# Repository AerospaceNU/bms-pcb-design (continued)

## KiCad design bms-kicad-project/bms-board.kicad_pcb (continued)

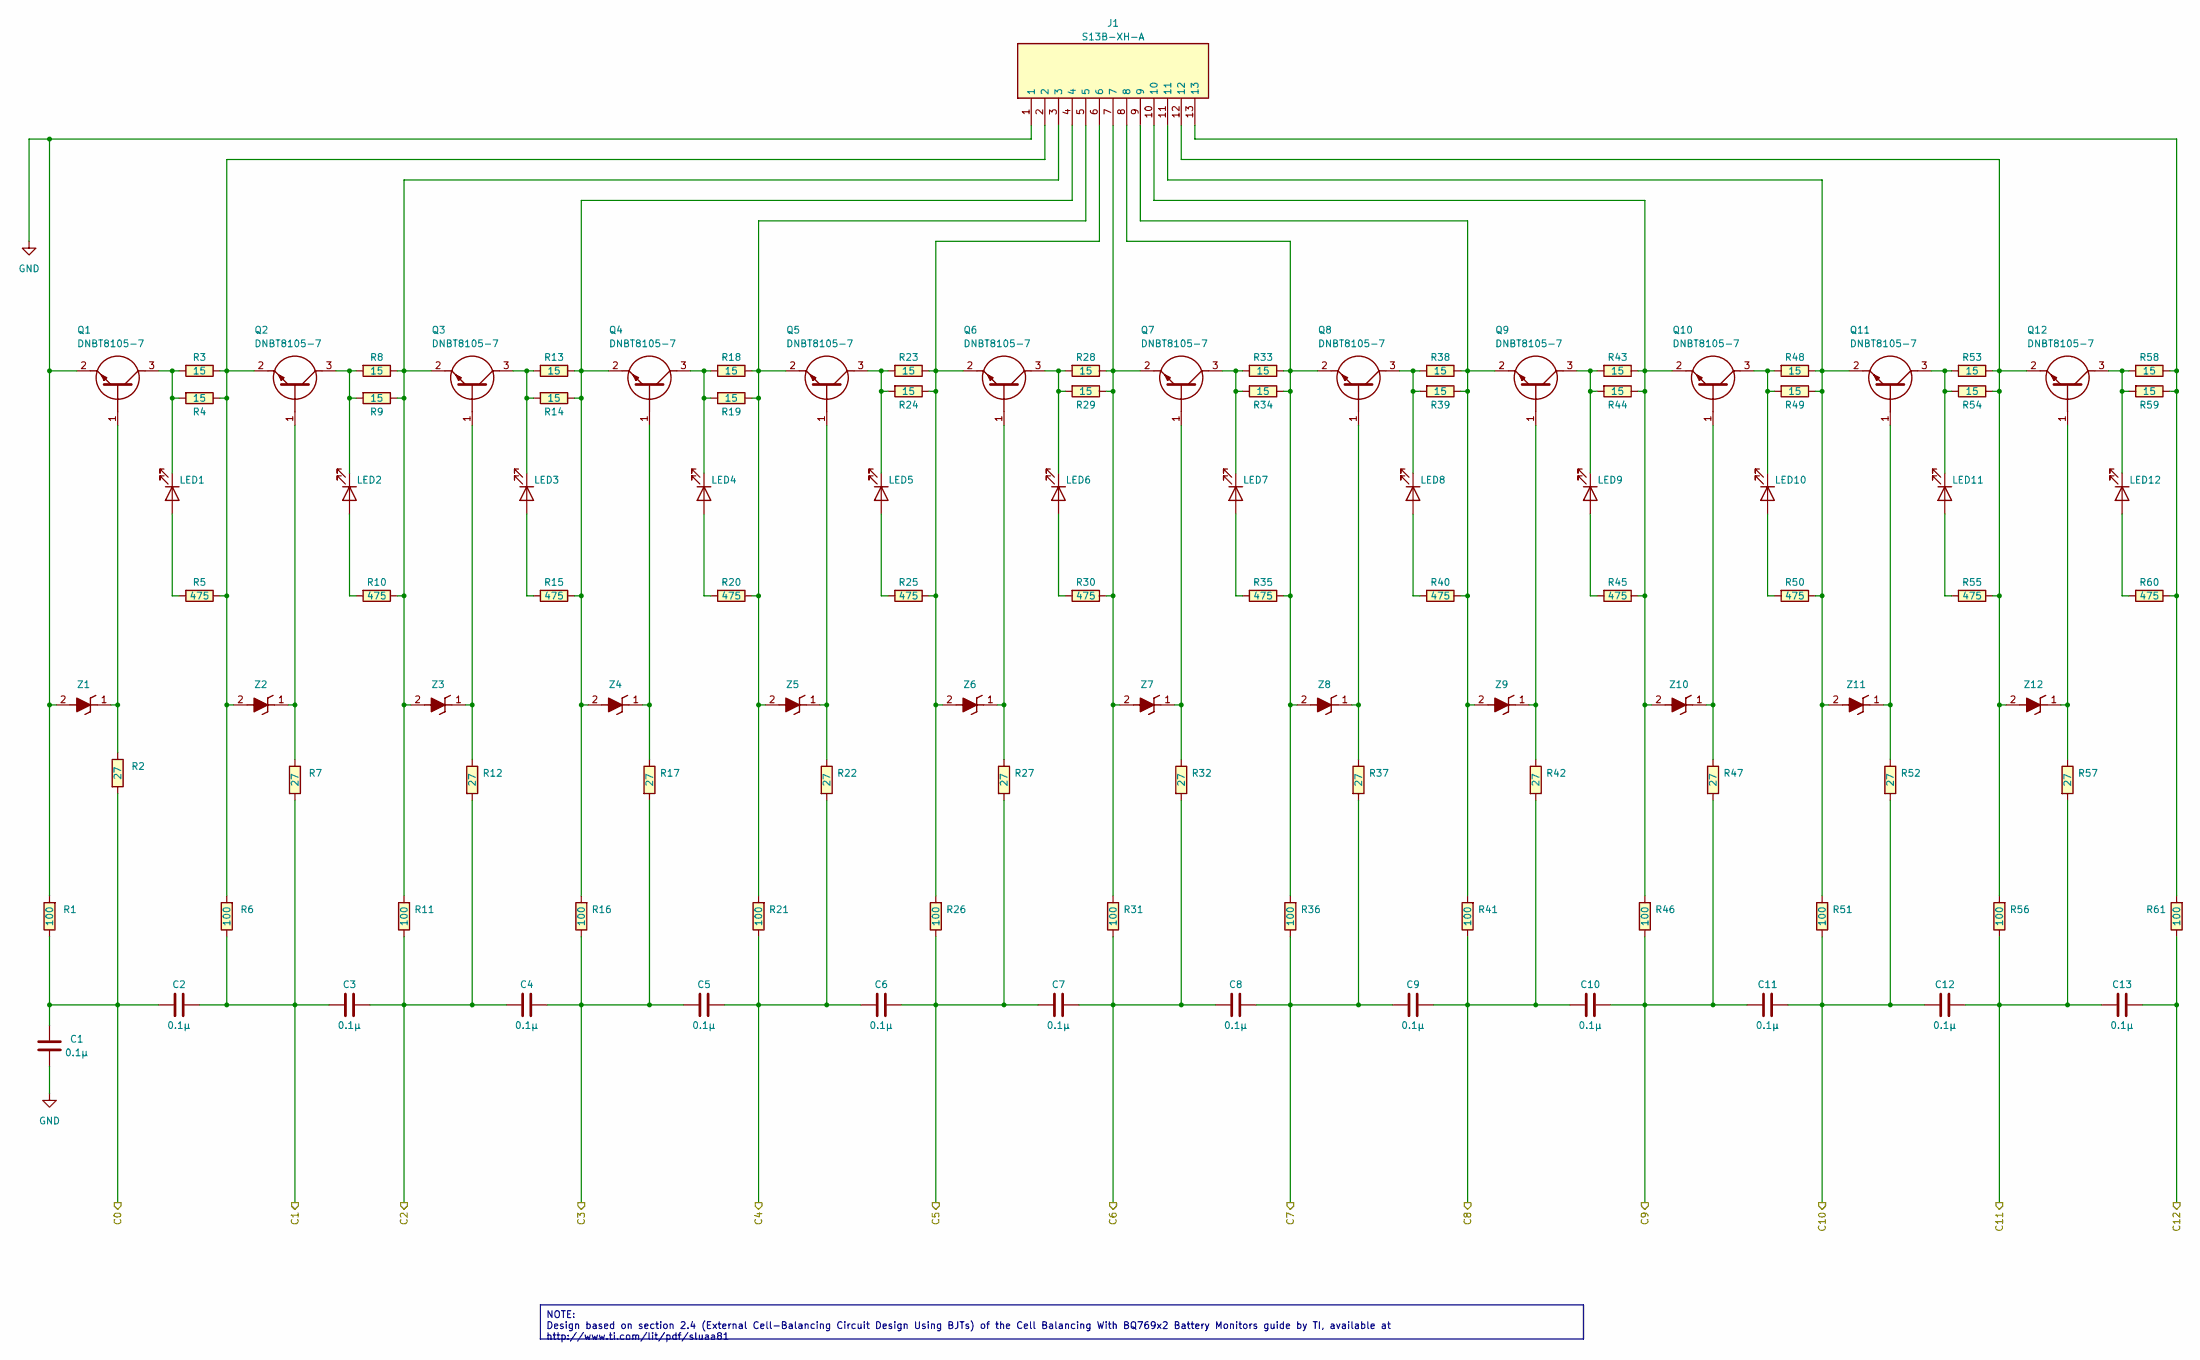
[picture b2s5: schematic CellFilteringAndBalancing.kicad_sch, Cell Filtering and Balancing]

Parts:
C1, C2, C3, C4, C5, C6, C7, C8, C9, C10, C11, C12, C13: 0.1µ; CAP_GCJ-18_MUR; Manufacturer Part Number GCJ188R72A104KA01D
J1: S13B-XH-A; S13BXHALFSN; Manufacturer Part Number S13B-XH-A
LED1, LED2, LED3, LED4, LED5, LED6, LED7, LED8, LED9, LED10, LED11, LED12: LTST-C170KRKT; LEDC2012X120N; Mouser Part Number 859-LTST-C170KRKT
Q1, Q2, Q3, Q4, Q5, Q6, Q7, Q8, Q9, Q10, Q11, Q12: DNBT8105-7; SOT95P240X105-3N; Manufacturer Part Number DNBT8105-7; Mouser Part Number 621-DNBT8105-7
R1, R6, R11, R16, R21, R26, R31, R36, R41, R46, R51, R56, R61: 100; RESC2012X50N; Mouser Part Number 71-CRCW0805-100-E3
R2, R7, R12, R17, R22, R27, R32, R37, R42, R47, R52, R57: 27; RC0805N_YAG; Manufacturer Part Number RC0805FR-0727RL
R3, R4, R8, R9, R13, R14, R18, R19, R23, R24, R28, R29, R33, R34, R38, R39, R43, R44, R48, R49, R53, R54, R58, R59: 15; RES_R1632_ROM; Manufacturer Part Number LTR18EZPF15R0
R5, R10, R15, R20, R25, R30, R35, R40, R45, R50, R55, R60: 475; RESC2012X50N; Mouser Part Number 71-CRCW0805-475-E3
Z1, Z2, Z3, Z4, Z5, Z6, Z7, Z8, Z9, Z10, Z11, Z12: BZT52C5V6T-7; BZT52C5V6T7; Manufacturer Part Number BZT52C5V6T-7; Mouser Part Number 621-BZT52C5V6T-7

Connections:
/Battery Stack Monitor/C0: C1.2, C2.2, R1.2, R2.1; also elsewhere on the board
/Battery Stack Monitor/C1: C2.1, C3.1, R6.2, R7.1; also elsewhere on the board
/Battery Stack Monitor/C2: C3.2, C4.1, R11.2, R12.1; also elsewhere on the board
/Battery Stack Monitor/C3: C4.2, C5.1, R16.2, R17.1; also elsewhere on the board
/Battery Stack Monitor/C4: C5.2, C6.1, R21.2, R22.1; also elsewhere on the board
/Battery Stack Monitor/C5: C6.2, C7.1, R26.2, R27.1; also elsewhere on the board
/Battery Stack Monitor/C6: C7.2, C8.1, R31.2, R32.1; also elsewhere on the board
/Battery Stack Monitor/C7: C8.2, C9.1, R36.2, R37.1; also elsewhere on the board
/Battery Stack Monitor/C8: C9.2, C10.1, R41.2, R42.1; also elsewhere on the board
/Battery Stack Monitor/C9: C10.2, C11.1, R46.2, R47.1; also elsewhere on the board
/Battery Stack Monitor/C10: C11.2, C12.1, R51.2, R52.1; also elsewhere on the board
/Battery Stack Monitor/C11: C12.2, C13.1, R56.2, R57.1; also elsewhere on the board
/Battery Stack Monitor/C12: C13.2, R61.2; also elsewhere on the board
GND: C1.1, J1.1, Q1.2 (E), R1.1, Z1.2 (A); also elsewhere on the board
unnamed: J1.13, R58.2, R59.2, R60.2, R61.1
unnamed: LED1.2 (A), R5.1
unnamed: LED1.1 (K), Q1.3 (C), R3.1, R4.1
unnamed: LED2.2 (A), R10.1
unnamed: LED2.1 (K), Q2.3 (C), R8.1, R9.1
unnamed: LED3.2 (A), R15.1
unnamed: LED3.1 (K), Q3.3 (C), R13.1, R14.1
unnamed: LED4.2 (A), R20.1
unnamed: LED4.1 (K), Q4.3 (C), R18.1, R19.1
unnamed: LED5.2 (A), R25.1
unnamed: LED5.1 (K), Q5.3 (C), R23.1, R24.1
unnamed: LED6.2 (A), R30.1
unnamed: LED6.1 (K), Q6.3 (C), R28.1, R29.1
unnamed: LED7.2 (A), R35.1
unnamed: LED7.1 (K), Q7.3 (C), R33.1, R34.1
unnamed: LED8.2 (A), R40.1
unnamed: LED8.1 (K), Q8.3 (C), R38.1, R39.1
unnamed: LED9.2 (A), R45.1
unnamed: LED9.1 (K), Q9.3 (C), R43.1, R44.1
unnamed: LED10.2 (A), R50.1
unnamed: LED10.1 (K), Q10.3 (C), R48.1, R49.1
unnamed: LED11.2 (A), R55.1
unnamed: LED11.1 (K), Q11.3 (C), R53.1, R54.1
unnamed: LED12.2 (A), R60.1
unnamed: LED12.1 (K), Q12.3 (C), R58.1, R59.1
unnamed: Q1.1 (B), R2.2, Z1.1 (K)
unnamed: Q2.1 (B), R7.2, Z2.1 (K)
unnamed: J1.2, Q2.2 (E), R3.2, R4.2, R5.2, R6.1, Z2.2 (A)
unnamed: Q3.1 (B), R12.2, Z3.1 (K)
unnamed: J1.3, Q3.2 (E), R8.2, R9.2, R10.2, R11.1, Z3.2 (A)
unnamed: Q4.1 (B), R17.2, Z4.1 (K)
unnamed: J1.4, Q4.2 (E), R13.2, R14.2, R15.2, R16.1, Z4.2 (A)
unnamed: Q5.1 (B), R22.2, Z5.1 (K)
unnamed: J1.5, Q5.2 (E), R18.2, R19.2, R20.2, R21.1, Z5.2 (A)
unnamed: Q6.1 (B), R27.2, Z6.1 (K)
unnamed: J1.6, Q6.2 (E), R23.2, R24.2, R25.2, R26.1, Z6.2 (A)
unnamed: Q7.1 (B), R32.2, Z7.1 (K)
unnamed: J1.7, Q7.2 (E), R28.2, R29.2, R30.2, R31.1, Z7.2 (A)
unnamed: Q8.1 (B), R37.2, Z8.1 (K)
unnamed: J1.8, Q8.2 (E), R33.2, R34.2, R35.2, R36.1, Z8.2 (A)
unnamed: Q9.1 (B), R42.2, Z9.1 (K)
unnamed: J1.9, Q9.2 (E), R38.2, R39.2, R40.2, R41.1, Z9.2 (A)
unnamed: Q10.1 (B), R47.2, Z10.1 (K)
unnamed: J1.10, Q10.2 (E), R43.2, R44.2, R45.2, R46.1, Z10.2 (A)
unnamed: Q11.1 (B), R52.2, Z11.1 (K)
unnamed: J1.11, Q11.2 (E), R48.2, R49.2, R50.2, R51.1, Z11.2 (A)
unnamed: Q12.1 (B), R57.2, Z12.1 (K)
unnamed: J1.12, Q12.2 (E), R53.2, R54.2, R55.2, R56.1, Z12.2 (A)

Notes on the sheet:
NOTE: Design based on section 2.4 (External Cell-Balancing Circuit Design Using BJTs) of the Cell Balancing With BQ769x2 Battery Monitors guide by TI, available at http://www.ti.com/lit/pdf/sluaa81

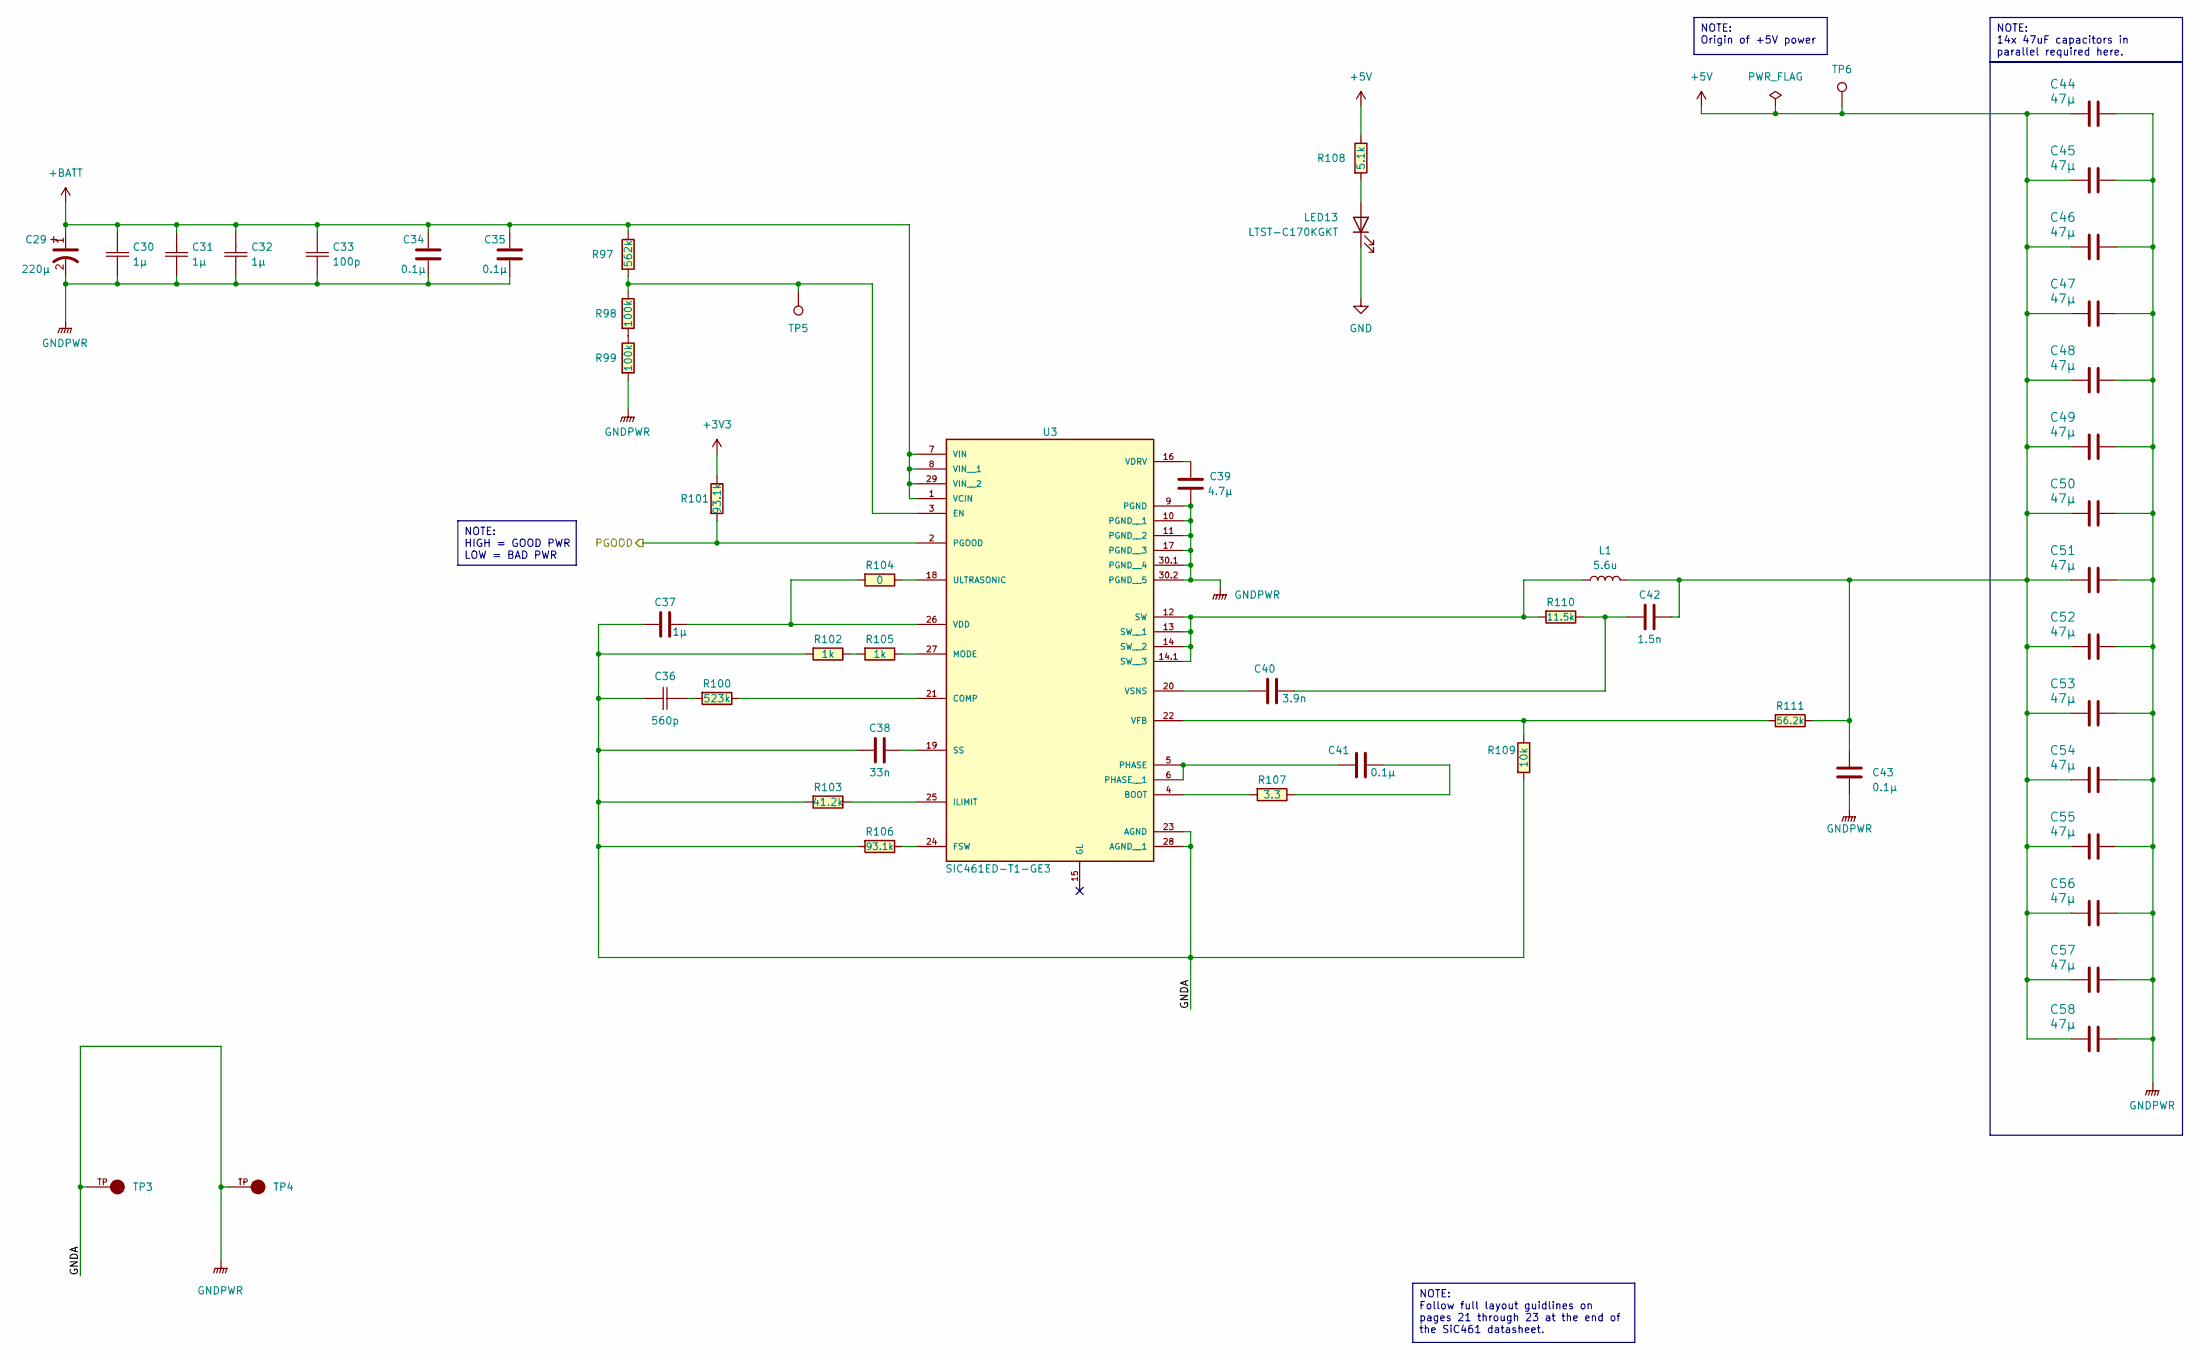
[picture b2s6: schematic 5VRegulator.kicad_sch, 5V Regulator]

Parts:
C29: 220µ; CAPPRD500W60D1000H2500; PARTREV 28-FEB-20
C30, C31, C32: 1µ; CAP_CL31_SAM; Manufacturer Part Number CL31B105KCHNNNE
C33: 100p; CAPC220145_88N_KEM; Manufacturer Part Number C0805C101J1GACTU
C34, C35: 0.1µ; CAP_GCJ-18_MUR; Manufacturer Part Number GCJ188R72A104KA01D
C36: 560p; CAP_CC0805_YAG; Manufacturer Part Number CC0805JRNPO9BN561
C37: 1µ; CAPC1608X90N; Manufacturer Part Number GCM188R71C105KA64D
C38: 33n; CAPC2012X94N; Manufacturer Part Number KGM21NR71E333KT
C39: 4.7µ; CAPC2012X145N; Manufacturer Part Number GCM21BC71E475KE36L
C40: 3.9n; G-21_MUR; Manufacturer Part Number GRM2165C1H392JA01D
C41, C43: 0.1µ; CAP_GCJ-18_MUR; Manufacturer_Part_Number GCJ188R72A104KA01D
C42: 1.5n; G-21_MUR; Manufacturer Part Number GRM2165C1H152JA01D
C44, C45, C46, C47, C48, C49, C50, C51, C52, C53, C54, C55, C56, C57, C58: 47µ; G-32_MUR; Manufacturer Part Number GRM32ER71A476KE15L
L1: 5.6u; IND_IHLP-6767GZ_VIS; Manufacturer Part Number IHLP6767GZER5R6M01
LED13: LTST-C170KGKT; LED_LTST-C170KGKT_LTO; Manufacturer Part Number LTST-C170KGKT
R97: 562k; RESC2012X60N; Manufacturer Part Number RC0805FR-07562KL
R98, R99: 100k; RESC2012X60N; Manufacturer Part Number RC0805FR-07100KL
R100: 523k; RC0805N_YAG; Manufacturer Part Number RC0805FR-07523KL
R101, R106: 93.1k; RESC2012X60N; Manufacturer Part Number RC0805FR-0793K1L
R102, R105: 1k; RC0805N_YAG; Manufacturer_Part_Number RC0805FR-071KL
R103: 41.2k; RC0805N_VIS; Manufacturer Part Number CRCW080541K2FKEA
R104: 0; RES_CRCW_0805_VIS; Manufacturer Part Number CRCW08050000Z0EA
R107: 3.3; RESC1608X55N; Manufacturer Part Number RK73H1JTTD3R30F
R108: 5.1k; RESC2012X60N; Manufacturer Part Number RC0805JR-075K1L
R109: 10k; KOA_Speer-RK73H2A-0-0-MFG; power rating 0.125W; tolerance 1%; Manufacturer Part Number RK73H2ATTD1002F; digikey description RES 10K OHM 1% 1/4W 0805
R110: 11.5k; RC0805N_YAG; Manufacturer Part Number RC0805FR-0711K5L
R111: 56.2k; RC0805N_YAG; Manufacturer Part Number RC0805FR-0756K2L
TP3, TP4: 5261; KEYSTONE_5261; PARTREV H
TP5, TP6: TestPoint_Pad_D1.0mm
U3: SIC461ED-T1-GE3; CONV_SIC461ED-T1-GE3; PARTREV M

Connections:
+3V3: R101.2; also elsewhere on the board
+5V: C42.2, C43.2, C44.2, C45.2, C46.2, C47.2, C48.2, C49.2, C50.2, C51.2, C52.2, C53.2, C54.2, C55.2, C56.2, C57.2, C58.2, L1.2, R108.2, R111.2, TP6.1; also elsewhere on the board
+BATT: C29.1, C30.2, C31.2, C32.2, C33.2, C34.2, C35.2, R97.2, U3.1 (VCIN), U3.7 (VIN), U3.8 (VIN__1), U3.29 (VIN__2); also elsewhere on the board
/5V Regulator/PGOOD: R101.1, U3.2 (PGOOD); also elsewhere on the board
GND: C29.2 (N), C30.1, C31.1, C32.1, C33.1, C34.1, C35.1, C36.1, C37.2, C38.1, C39.1, C43.1, C44.1, C45.1, C46.1, C47.1, C48.1, C49.1, C50.1, C51.1, C52.1, C53.1, C54.1, C55.1, C56.1, C57.1, C58.1, LED13.1 (K), R99.1, R102.1, R103.1, R106.1, R109.1, TP3.TP, TP4.TP, U3.9 (PGND), U3.10 (PGND__1), U3.11 (PGND__2), U3.17 (PGND__3), U3.23 (AGND), U3.28 (AGND__1), U3.30.1 (PGND__4), U3.30.2 (PGND__5); also elsewhere on the board
unnamed: C36.2, R100.1
unnamed: C40.2, C42.1, R110.2
unnamed: C41.1, R107.2
unnamed: LED13.2 (A), R108.1
unnamed: R98.1, R99.2
unnamed: R102.2, R105.1
unnamed: R107.1, U3.4 (BOOT)
unnamed: R100.2, U3.21 (COMP)
unnamed: R97.1, R98.2, TP5.1, U3.3 (EN)
unnamed: R106.2, U3.24 (FSW)
unnamed: R103.2, U3.25 (ILIMIT)
unnamed: R105.2, U3.27 (MODE)
unnamed: C41.2, U3.5 (PHASE), U3.6 (PHASE__1)
unnamed: C38.2, U3.19 (SS)
unnamed: L1.1, R110.1, U3.12 (SW), U3.13 (SW__1), U3.14 (SW__2), U3.14.1 (SW__3)
unnamed: R104.2, U3.18 (ULTRASONIC)
unnamed: C37.1, R104.1, U3.26 (VDD)
unnamed: C39.2, U3.16 (VDRV)
unnamed: R109.2, R111.1, U3.22 (VFB)
unnamed: C40.1, U3.20 (VSNS)

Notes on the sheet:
NOTE: 14x 47uF capacitors in parallel required here.
NOTE: Origin of +5V power
NOTE: Follow full layout guidlines on pages 21 through 23 at the end of the SiC461 datasheet.
NOTE: HIGH = GOOD PWR LOW = BAD PWR

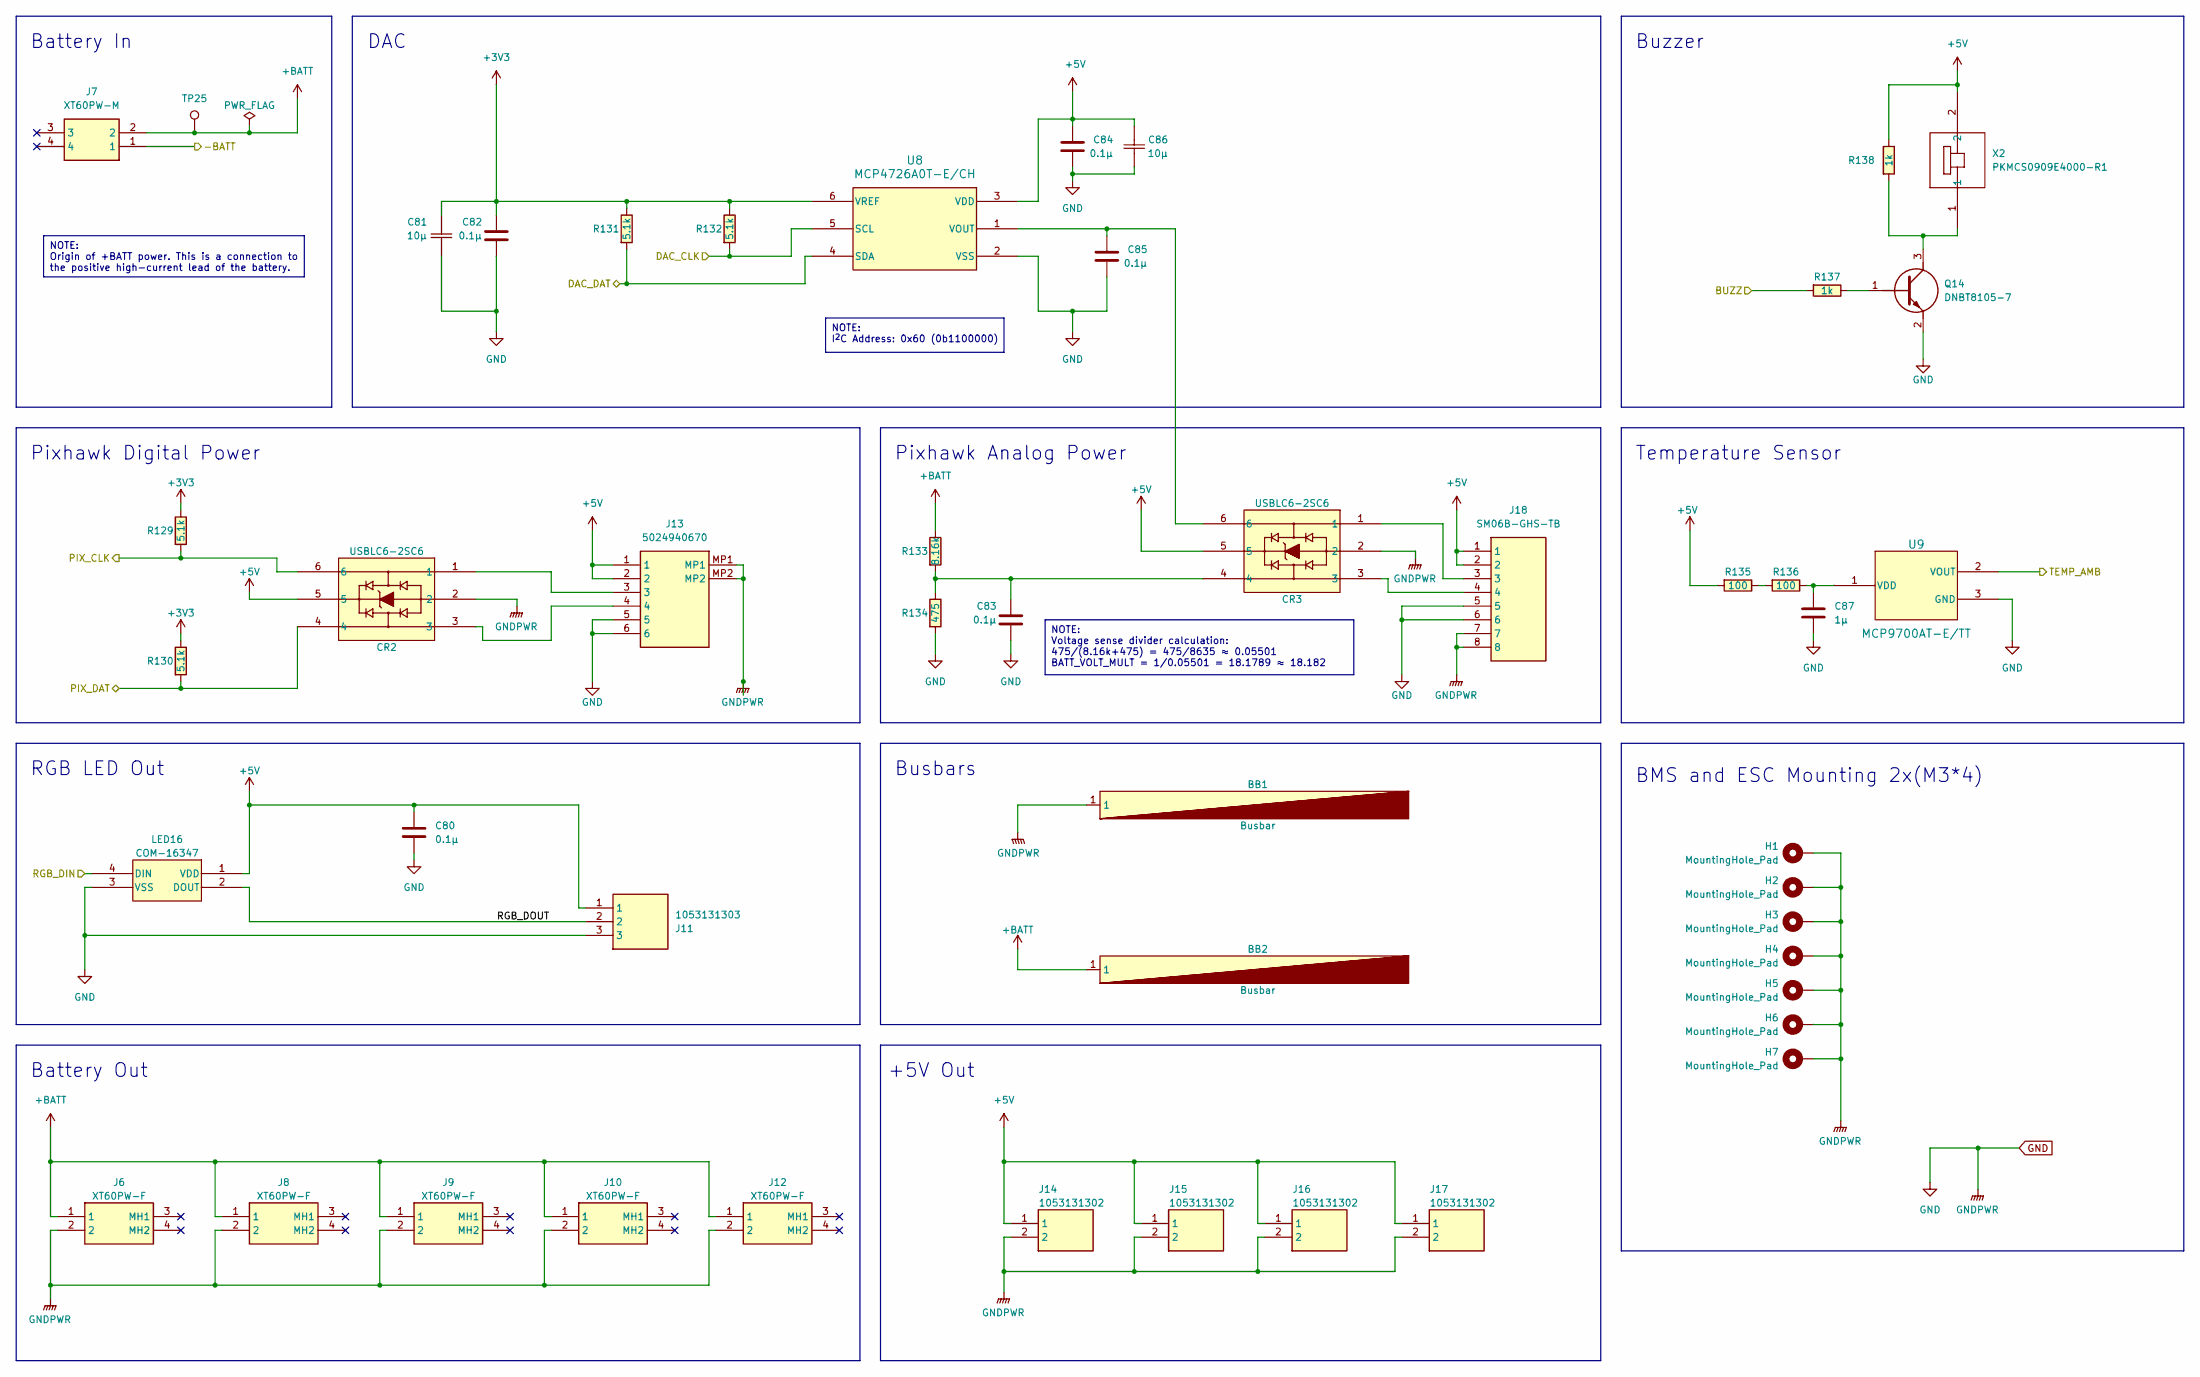
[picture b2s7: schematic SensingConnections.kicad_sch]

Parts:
BB1: Busbar; BUSBAR_SHORT; Manufacturer Part Number T2 Copper
BB2: Busbar; BUSBAR_LONG; Manufacturer Part Number T2 Copper
C80, C82, C83, C84, C85: 0.1µ; CAP_GCJ-18_MUR; Manufacturer Part Number GCJ188R72A104KA01D
C81, C86: 10µ; CAP_CL21B106KOQNNNE_SAM; Manufacturer Part Number CL21B106KOQNNNE
C87: 1µ; CAPC1608X90N; Manufacturer Part Number GCM188R71C105KA64D
CR2, CR3: USBLC6-2SC6; SOT23-6L_STM; Manufacturer Part Number USBLC6-2SC6
H1, H2, H3, H4, H5, H6, H7: MountingHole_Pad; MountingHole_3.2mm_M3_ISO14580_Pad
J6, J8, J9, J10: XT60PW-F; XT60PWF; Manufacturer Part Number XT60PW-F
J7: XT60PW-M; XT60PWM_Pad; Manufacturer Part Number XT60PW-M
J11: 1053131303; 105313YY03; Manufacturer Part Number 1053131303
J12: XT60PW-F; XT60PWF_Pad; Manufacturer Part Number XT60PW-F
J13: 5024940670; Manufacturer Part Number 5024940670; Mouser Part Number 538-502494-0670
J14, J15, J16, J17: 1053131302; 105313YY02; Manufacturer Part Number 1053131302
J18: SM06B-GHS-TB; Manufacturer Part Number SM06B-GHS-TB(LF)(SN); Mouser Part Number 306-SM06BGHSTBLFSN
LED16: COM-16347; COM-16347_SPK; Manufacturer Part Number COM-16347
Q14: DNBT8105-7; SOT95P240X105-3N; Manufacturer Part Number DNBT8105-7; Mouser Part Number 621-DNBT8105-7
R129, R130, R131, R132: 5.1k; RESC2012X60N; Manufacturer Part Number RC0805JR-075K1L
R133: 8.16k; RC0805N_YAG; Manufacturer Part Number RT0805BRD078K16L
R134: 475; RESC2012X50N; Mouser Part Number 71-CRCW0805-475-E3
R135, R136: 100; RESC2012X50N; Mouser Part Number 71-CRCW0805-100-E3
R137, R138: 1k; RC0805N_YAG; Manufacturer Part Number RC0805FR-071KL
TP25: TestPoint_Pad_D1.0mm
U8: MCP4726A0T-E/CH; SOT-23-6_MC_MCH; Manufacturer Part Number MCP4726A0T-E/CH
U9: MCP9700AT-E/TT; SOT-23_MC_MCH; Manufacturer Part Number MCP9700AT-E/TT
X2: PKMCS0909E4000-R1; PKMCS0909E4000-R1_MUR; Manufacturer Part Number PKMCS0909E4000-R1

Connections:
+3V3: C81.2, C82.2, R129.2, R130.2, R131.2, R132.2, U8.6 (VREF); also elsewhere on the board
+5V: C80.2, C84.2, C86.2, CR2.5, CR3.5, J11.1, J13.1, J13.2, J14.1, J15.1, J16.1, J17.1, J18.1, J18.2, LED16.1 (VDD), R135.1, R138.2, U8.3 (VDD), X2.2; also elsewhere on the board
+BATT: BB2.1, J6.1, J7.2, J8.1, J9.1, J10.1, J12.1, R133.1, TP25.1; also elsewhere on the board
/Battery Stack Monitor/-BATT: J7.1; also elsewhere on the board
/External Connections and Sensing/BUZZ: R137.1; also elsewhere on the board
/External Connections and Sensing/DAC_CLK: R132.1, U8.5 (SCL); also elsewhere on the board
/External Connections and Sensing/DAC_DAT: R131.1, U8.4 (SDA); also elsewhere on the board
/External Connections and Sensing/PIX_CLK: CR2.6, R129.1; also elsewhere on the board
/External Connections and Sensing/PIX_DAT: CR2.4, R130.1; also elsewhere on the board
/External Connections and Sensing/RGB_DIN: LED16.4 (DIN); also elsewhere on the board
/External Connections and Sensing/RGB_DOUT: J11.2, LED16.2 (DOUT)
/External Connections and Sensing/TEMP_AMB: U9.2 (VOUT); also elsewhere on the board
GND: BB1.1, C80.1, C81.1, C82.1, C83.1, C84.1, C85.1, C86.1, C87.1, CR2.2, CR3.2, H1.1, H2.1, H3.1, H4.1, H5.1, H6.1, H7.1, J6.2, J8.2, J9.2, J10.2, J11.3, J12.2, J13.5, J13.6, J13.MP1, J13.MP2, J14.2, J15.2, J16.2, J17.2, J18.5, J18.6, J18.7, J18.8, LED16.3 (VSS), Q14.2 (E), R134.1, U8.2 (VSS), U9.3 (GND); also elsewhere on the board
unnamed: C83.2, CR3.4, R133.2, R134.2
unnamed: CR2.1, J13.3
unnamed: CR2.3, J13.4
unnamed: CR3.1, J18.3
unnamed: CR3.3, J18.4
unnamed: Q14.1 (B), R137.2
unnamed: Q14.3 (C), R138.1, X2.1
unnamed: R135.2, R136.1
unnamed: C85.2, CR3.6, U8.1 (VOUT)
unnamed: C87.2, R136.2, U9.1 (VDD)

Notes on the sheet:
NOTE: Voltage sense divider calculation: 475/(8.16k+475) = 475/8635 ≈ 0.05501 BATT_VOLT_MULT = 1/0.05501 = 18.1789 ≈ 18.182
NOTE: I^{2}C Address: 0x60 (0b1100000)
NOTE: Origin of +BATT power. This is a connection to the positive high-current lead of the battery.
Battery In
Buzzer
RGB LED Out
Battery Out
DAC
Pixhawk Analog Power
BMS and ESC Mounting 2x(M3*4)
Pixhawk Digital Power
Temperature Sensor
+5V Out
Busbars

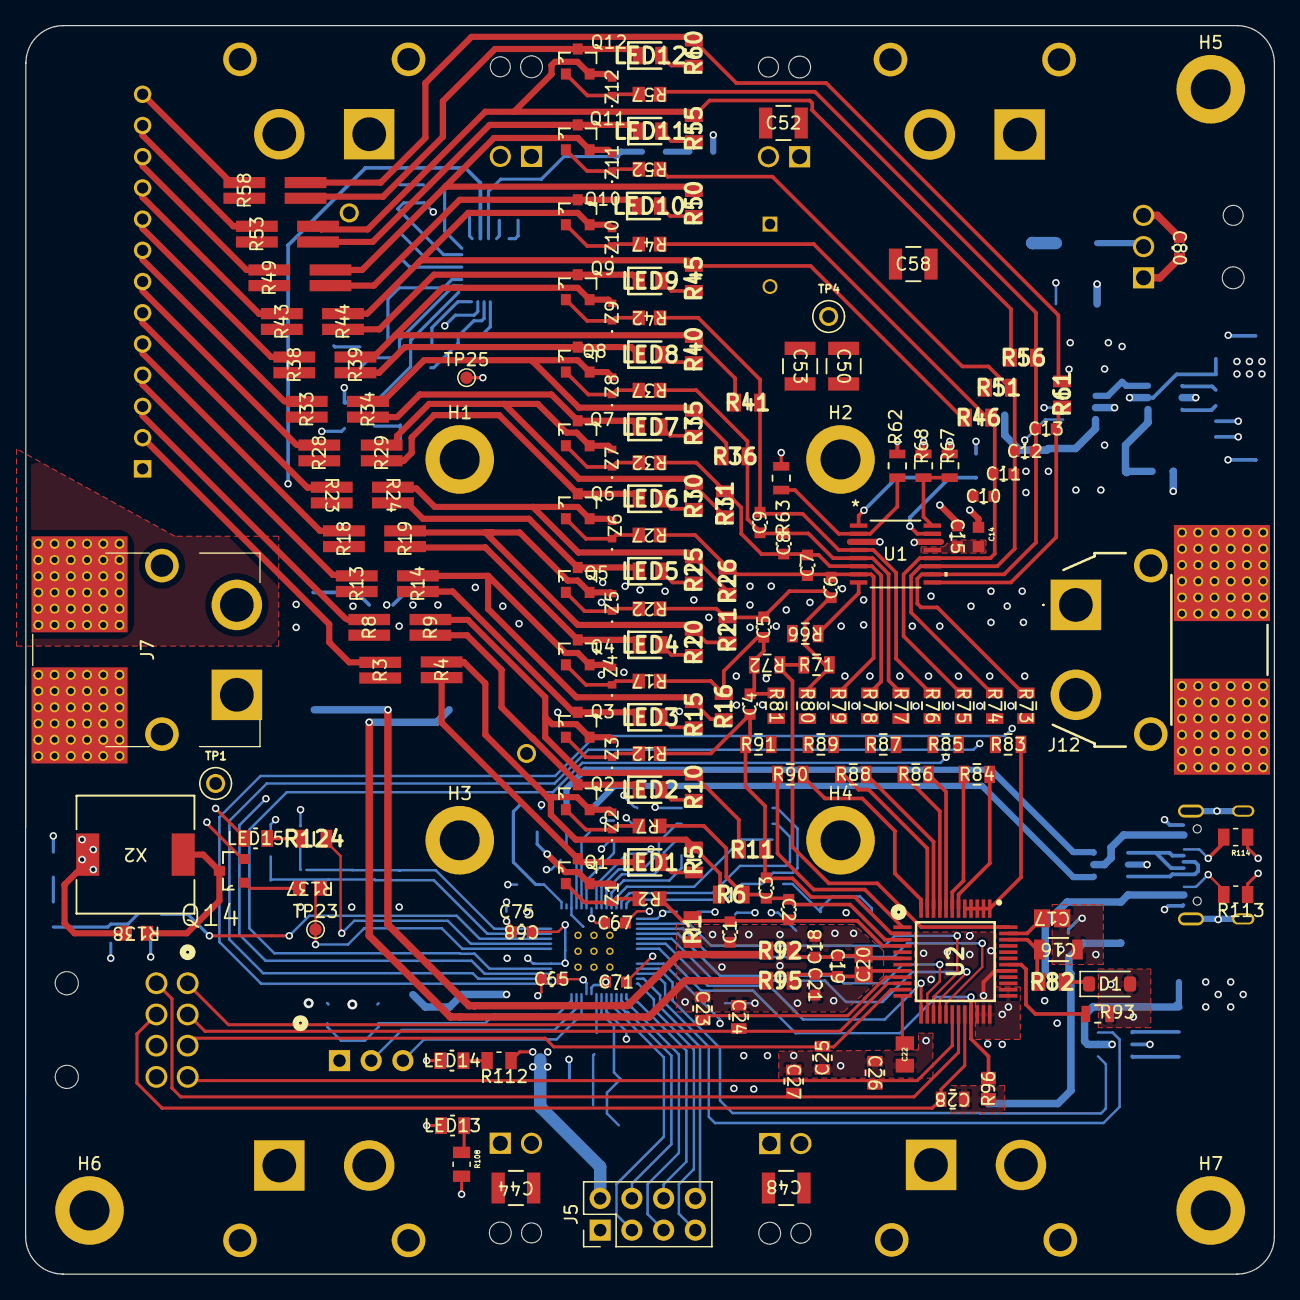
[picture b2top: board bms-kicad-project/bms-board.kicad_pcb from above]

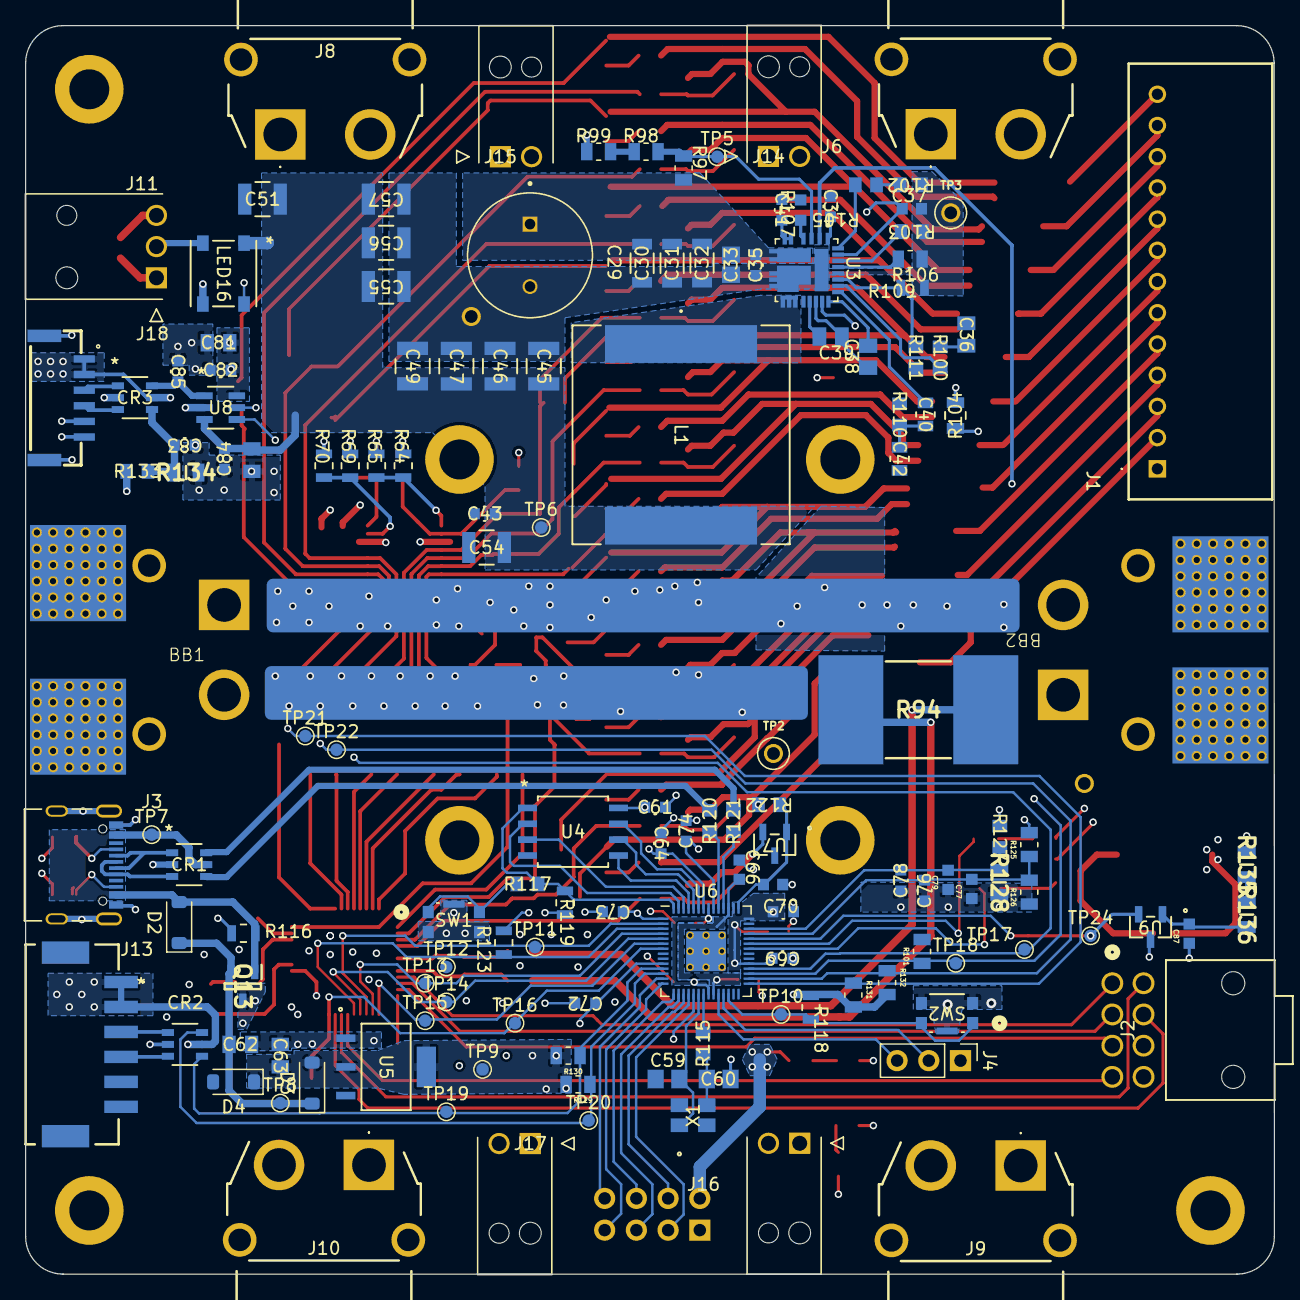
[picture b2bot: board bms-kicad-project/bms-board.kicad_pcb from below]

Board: 6 copper layers, 100.0 x 100.0 mm, 340 parts (145 on the bottom side), 174 nets.

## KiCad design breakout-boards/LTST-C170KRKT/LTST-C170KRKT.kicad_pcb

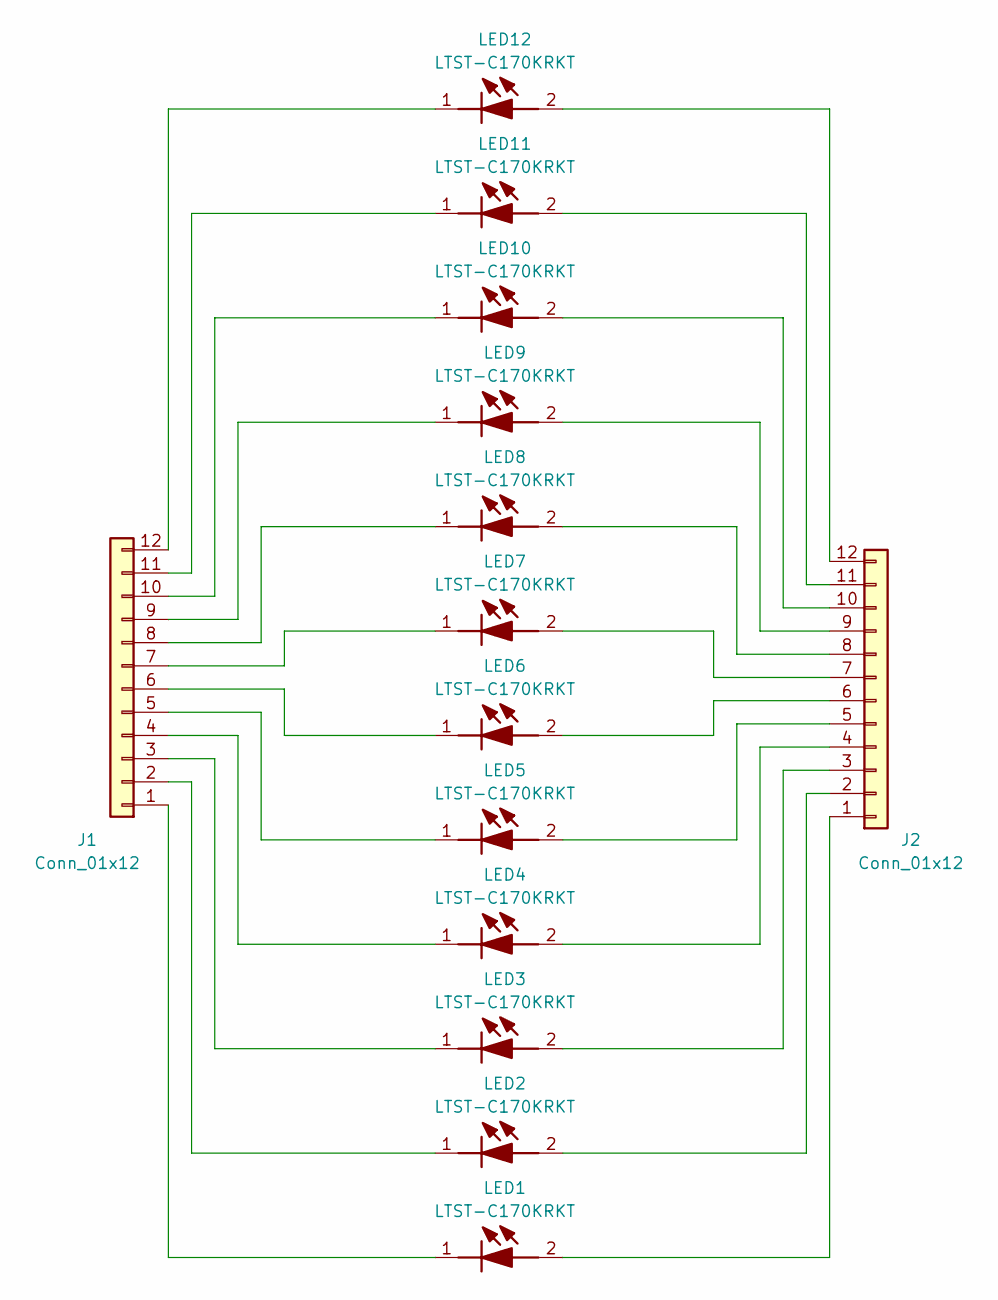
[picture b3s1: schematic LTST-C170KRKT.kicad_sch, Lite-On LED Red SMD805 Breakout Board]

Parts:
J1, J2: Conn_01x12; PinSocket_1x12_P2.54mm_Vertical
LED1, LED2, LED3, LED4, LED5, LED6, LED7, LED8, LED9, LED10, LED11, LED12: LTST-C170KRKT; LEDC2012X120N; Mouser Part Number 859-LTST-C170KRKT

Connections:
unnamed: J1.1, LED1.1 (K)
unnamed: J1.2, LED2.1 (K)
unnamed: J1.3, LED3.1 (K)
unnamed: J1.4, LED4.1 (K)
unnamed: J1.5, LED5.1 (K)
unnamed: J1.6, LED6.1 (K)
unnamed: J1.7, LED7.1 (K)
unnamed: J1.8, LED8.1 (K)
unnamed: J1.9, LED9.1 (K)
unnamed: J1.10, LED10.1 (K)
unnamed: J1.11, LED11.1 (K)
unnamed: J1.12, LED12.1 (K)
unnamed: J2.1, LED1.2 (A)
unnamed: J2.2, LED2.2 (A)
unnamed: J2.3, LED3.2 (A)
unnamed: J2.4, LED4.2 (A)
unnamed: J2.5, LED5.2 (A)
unnamed: J2.6, LED6.2 (A)
unnamed: J2.7, LED7.2 (A)
unnamed: J2.8, LED8.2 (A)
unnamed: J2.9, LED9.2 (A)
unnamed: J2.10, LED10.2 (A)
unnamed: J2.11, LED11.2 (A)
unnamed: J2.12, LED12.2 (A)

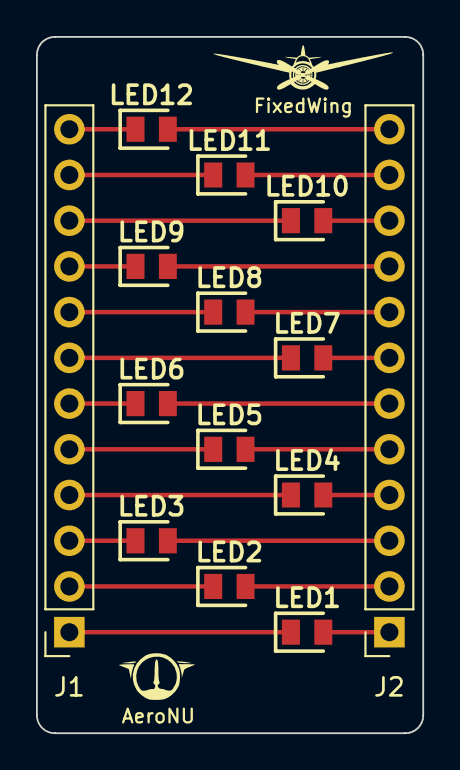
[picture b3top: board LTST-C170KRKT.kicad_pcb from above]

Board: 2 copper layers, 21.5 x 38.7 mm, 16 parts (0 on the bottom side), 24 nets.

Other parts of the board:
AeroNU: LOGO; AeroNU - Logo (Smol)
FixedWing: LOGO; FixedWing - Logo (Smol)
